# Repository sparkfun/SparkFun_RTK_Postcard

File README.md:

SparkFun RTK Postcard
========================================

[*SparkFun RTK Postcard (GPS-26916)*](https://www.sparkfun.com/sparkfun-rtk-postcard.html)

Designed and manufactured in Boulder, CO USA, the [SparkFun RTK Postcard](https://www.sparkfun.com/sparkfun-rtk-postcard.html) is a compact development board for your high-precision positioning and navigation needs. This board combines the Quectel LG290P GNSS RTK receiver with an Espressif ESP32-PICO-MINI-02 MCU module, running our latest [RTK Everywhere firmware](https://github.com/sparkfun/SparkFun_RTK_Everywhere_Firmware). The ESP32 provides the SparkFun Postcard with WiFi and Bluetooth&trade; connectivity to operate as an NTRIP caster or client. Meanwhile, the 4-pin locking JST-GH connector allows users to transmit or receive RTCMv3 messages for RTK corrections from a local base station.

- The LG290P module is a quad-band, multi-constellation, high-precision, RTK GNSS receiver. The module can simultaneously receive signals from the `L1`, `L2`, `L5`, and `L6`/`E6` frequency bands of the GPS, GLONASS, Galileo, BDS, QZSS, and NavIC GNSS constellations. In addition, the module supports SBAS augmentation systems (WASS, EGNOS, BDSBAS, MSAS, GAGAN, and SDCM), PPP services* (BDS PPP-B2b, QZSS CLAS, MADOCA-PPP, and Galileo HAS), RTCM, and RTK corrections for precision navigation with a fast convergence time and reliable performance. Connect with ease using a variety of interfaces, including UART, SPI*, and I2C*. 

- The ESP32-PICO-MINI-02 is a powerful MCU module with WiFi, Bluetooth&trade;, and BLE connectivity and comes integrated with 8MB SPI flash, 2MB SPI Pseudo static RAM (PSRAM), and a 40 MHz crystal oscillator. The ESP32 microcontroller itself features two CPU cores that can be individually controlled, with an adjustable clock frequency between 80 - 240MHz and a low-power co-processor for minor tasks, such as monitoring peripherals. It supports a range of peripherals including an SD card interface, capacitive touch sensors, ADC, DAC, Two-Wire Automotive Interface (TWAI), Ethernet, high-speed SPI, UART, I2S, I2C, etc.

With the [RTK Everywhere firmware](https://github.com/sparkfun/SparkFun_RTK_Everywhere_Firmware) that comes pre-loaded, users can seamlessly operate the RTK Postcard as a base station or rover. These modes also offer additional functions, based on the available, wireless communication options:

- The RTK Postcard can transmit or receive RTCMv3 messages locally by connecting one of our [SiK Telemetry radios](https://www.sparkfun.com/sik-telemetry-radio-v3-915mhz-100mw.html).
- Through WiFi or Bluetooth&trade;, the RTK Postcard can also function as an NTRIP caster or client.
- The RTK Postcard can transmit NMEA messages to a [graphical information software (GIS)](https://docs.sparkfun.com/SparkFun_RTK_Everywhere_Firmware/gis_software_android/) apps on any mobile device when paired as a Bluetooth&trade; device.

In addition to the RTK Postcard, we created the [Portability Shield](https://www.sparkfun.com/sparkfun-portability-shield.html) for the convenience of users. Simply connecting these products, provides a 1.3” OLED display and a five-way button to navigate the configuration settings and display PNT data; a microSD card slot for data logging; and a LiPo battery charger with a fuel gauge to take the RTK Postcard *"on-the-go"*. All of these will operate plug-and-play without the need for new code.

> [!NOTE]
> The [RTK Everywhere firmware](https://github.com/sparkfun/SparkFun_RTK_Everywhere_Firmware) is open-source, so users can obtain, check, and even modify the device's functionality. This allows for easier feature expansion, bug maintenance, and longer device longevity.

> [!NOTE]
> `*`: Feature is still under development

> [!IMPORTANT]
> - Currently, only the UART interface is supported by the LG290P module.
> - Additionally, the corrections for some of the PPP services may not be implemented yet.

Documentation
--------------

* **[Hookup Guide (mkdocs)](http://docs.sparkfun.com/SparkFun_RTK_Postcard/)** - The hookup guide for the SparkFun RTK Postcard hosted by GitHub pages.<br>
   
* [User Manual - RTK Everywhere Firmware](https://docs.sparkfun.com/SparkFun_RTK_Everywhere_Firmware/) - Documentation for the [RTK Everywhere firmware](https://github.com/sparkfun/SparkFun_RTK_Everywhere_Firmware)
* [SparkFun LG290P GNSS Arduino Library](https://github.com/sparkfun/SparkFun_LG290P_GNSS_Arduino_Library) - An Arduino library for the LG290P and LGx80P GNSS modules

*Need to download or print our hookup guide?*

* [Print *(Print to PDF)* from Single-Page View](http://docs.sparkfun.com/SparkFun_RTK_Postcard/print_view)

Repository Contents
-------------------

* **[/docs](/docs/)** - Online documentation files
    * [assets](/docs/assets/) - Assets files
        * [3d_model](/docs/assets/3d_model/) - Files for the 3D models
            * [3D CAD Model](/docs/assets/3d_model/cad_model.step) (.step)
        * [board_files](/docs/assets/board_files/) - Files for the product design
            * [KiCad Design Files](/docs/assets/board_files/kicad_files.zip) (.zip)
            * [Schematic](/docs/assets/board_files/schematic.pdf) (.pdf)
            * [Dimensions](/docs/assets/board_files/dimensions.pdf) (.pdf)
        * [component_documentation](/docs/assets/component_documentation/) - Datasheets for hardware components
        * [img/hookup_guide/](/docs/assets/img/hookup_guide/) - Images for hookup guide documentation
* **[/Enclosure](/Enclosure/)** - CAD model for an enclosure
* **[/Hardware](/Hardware/)** - Hardware design files (.brd, .sch)
  * **[/Production](/Production/)** - Production files

Product Variants
----------------

- LG290P Variants
  - [GPS-26916](https://www.sparkfun.com/sparkfun-rtk-postcard.html) - v1.0, Initial Release
  - [GPS-26620](https://www.sparkfun.com/sparkfun-quadband-gnss-rtk-breakout-lg290p-qwiic.html) - SparkFun Quadband GNSS RTK Breakout - LG290P (Qwiic) *(w/o ESP32)*
- [GPS-28019](https://www.sparkfun.com/products/28019) - SparkFun Quadband GNSS RTK Breakout - LG580P (Qwiic)

Version History
---------------

* [v10](https://github.com/sparkfun/SparkFun_RTK_Postcard/releases/tag/v10) - Initial Release

License Information
-------------------

This product is ***open source***!

Please review the [`LICENSE.md`](./LICENSE.md) file for license information.

If you have any questions or concerns about licensing, please contact technical support on our [SparkFun forums](https://community.sparkfun.com/).

Distributed as-is; no warranty is given.

- Your friends at SparkFun.

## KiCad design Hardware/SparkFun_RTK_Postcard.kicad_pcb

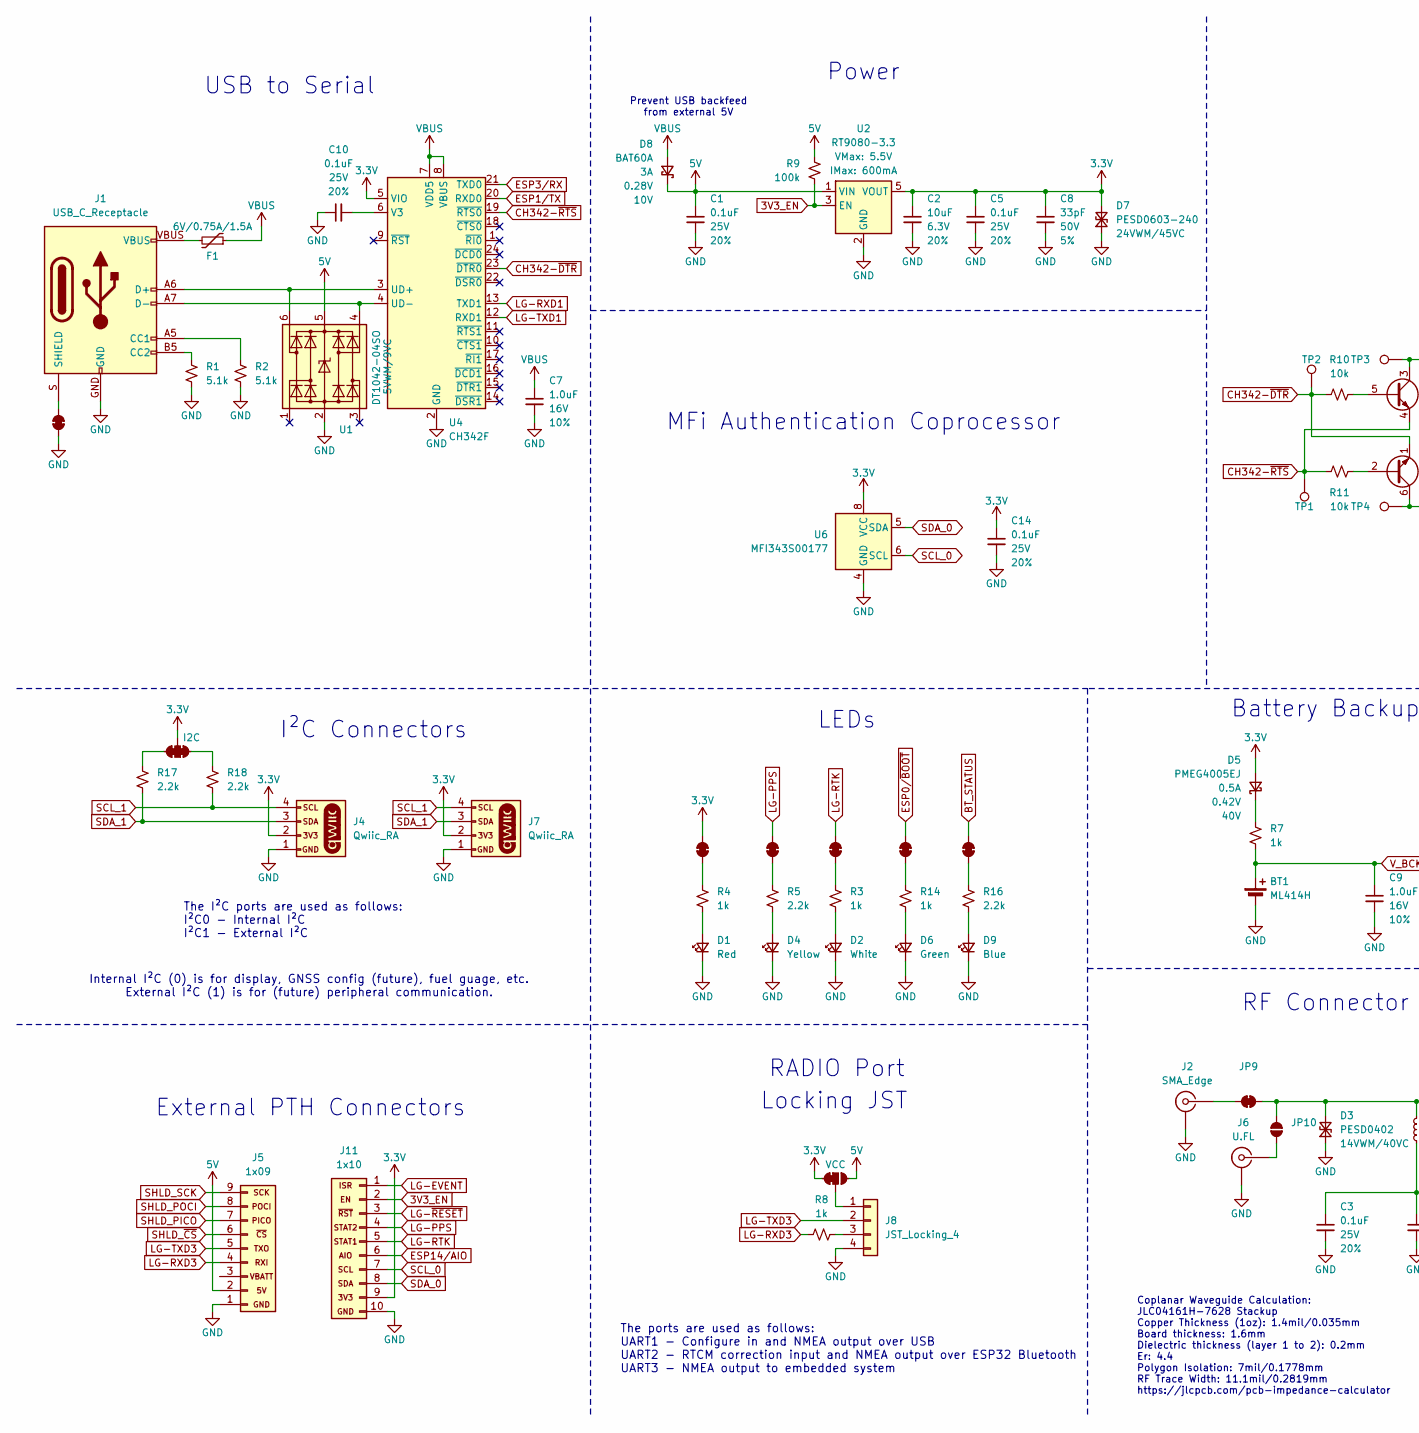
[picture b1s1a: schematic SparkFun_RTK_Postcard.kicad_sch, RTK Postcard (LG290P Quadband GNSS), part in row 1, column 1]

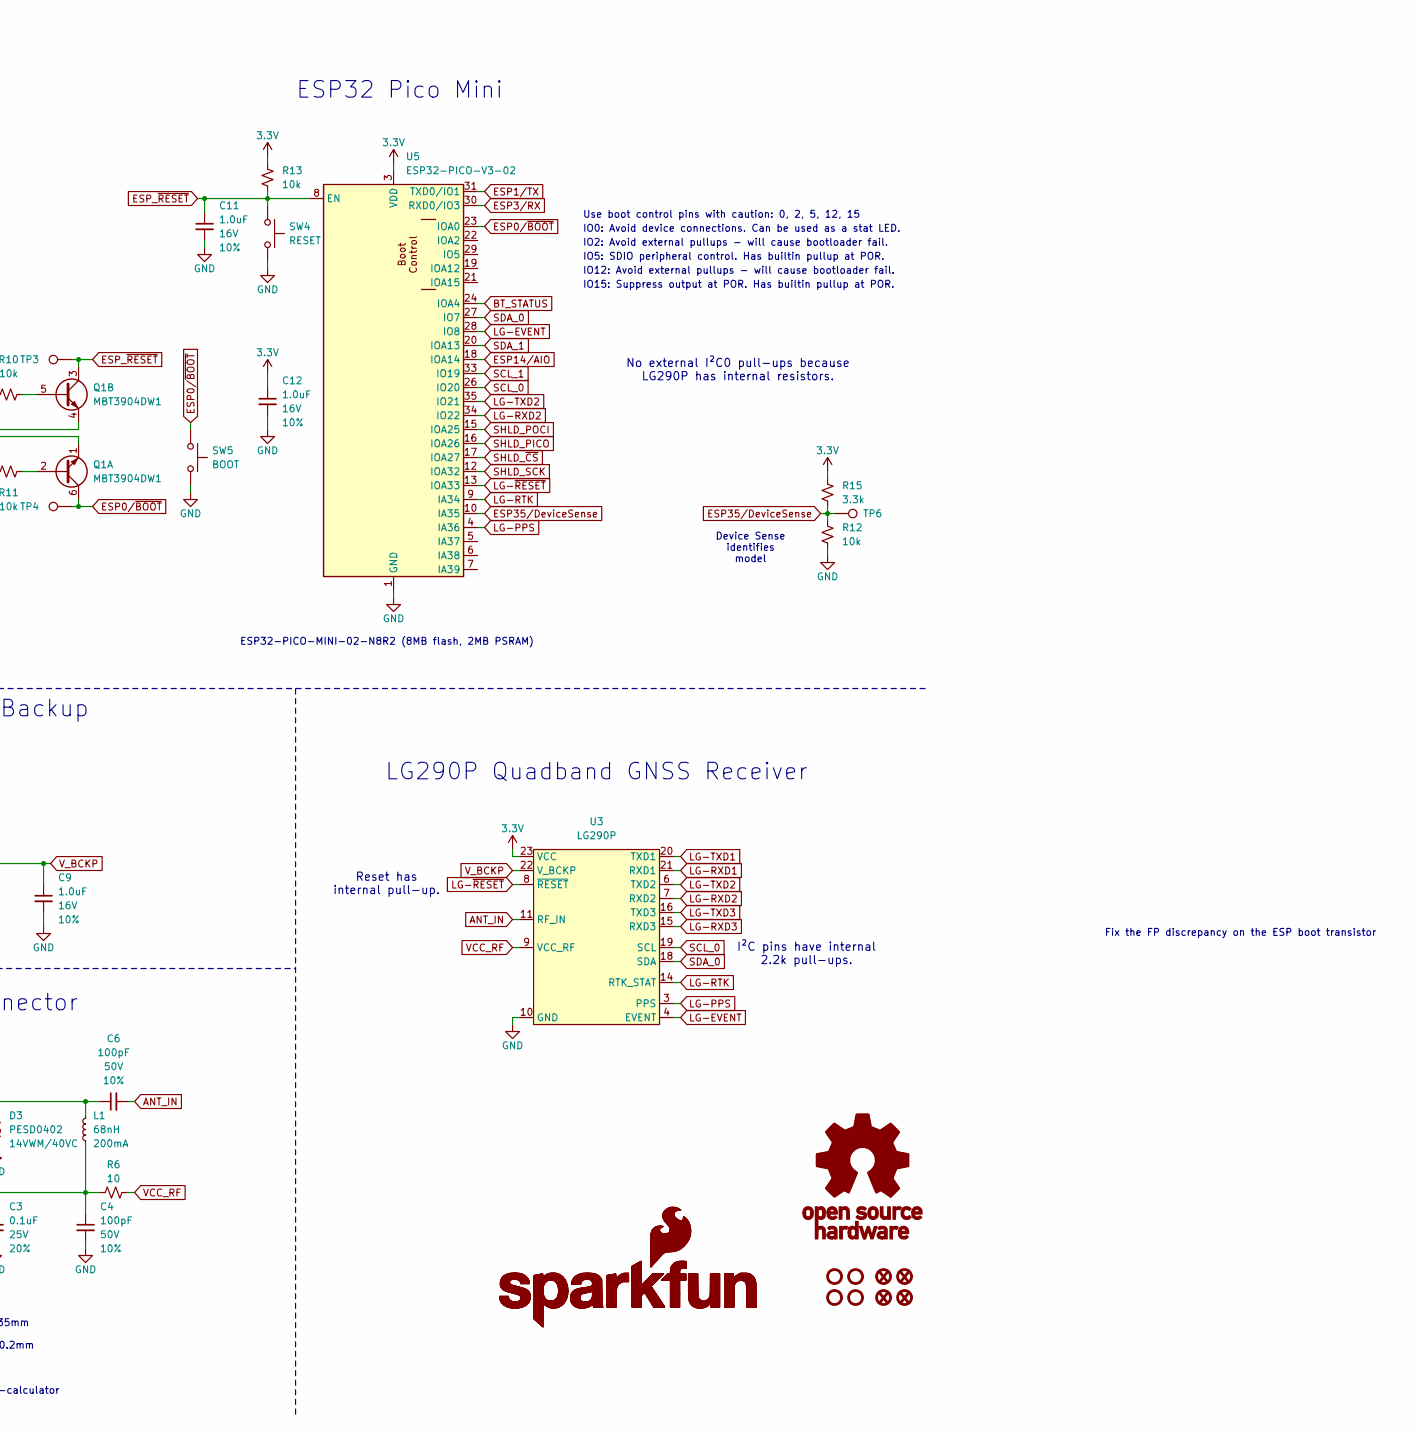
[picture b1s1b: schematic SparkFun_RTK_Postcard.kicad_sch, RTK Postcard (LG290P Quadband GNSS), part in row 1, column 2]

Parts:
BT1: ML414H; ML414H_IV01E
C1, C3, C5, C10, C14: 0.1uF; C_0603_1608Metric; Voltage 25V; Tolerance 20%
C2: 10uF; C_0603_1608Metric; Voltage 6.3V; Tolerance 20%
C4: 100pF; C_0603_1608Metric; Voltage 50V; Tolerance 10%
C6: 100pF; C_0402_1005Metric; Voltage 50V; Tolerance 10%
C7, C9, C11, C12: 1.0uF; C_0603_1608Metric; Voltage 16V; Tolerance 10%
C8: 33pF; C_0603_1608Metric; Voltage 50V; Tolerance 5%
D1: Red; LED_0603_1608Metric_Red
D2: White; LED_0603_1608Metric_White
D3: PESD0402; C_0402_1005Metric; Rating 14VWM/40VC
D4: Yellow; LED_0603_1608Metric_Yellow
D5: PMEG4005EJ; SOD-323
D6: Green; LED_0603_1608Metric_Green
D7: PESD0603-240; C_0603_1608Metric; Rating 24VWM/45VC
D8: BAT60A; SOD-323
D9: Blue; LED_0603_1608Metric_Blue
F1: 6V/0.75A/1.5A; 1206
FID1, FID2, FID3, FID4: Fiducial_0.5mm; Fiducial_0.5mm_Mask1mm
G1: OSHW_Logo; Creative_Commons_License
G3, G5: SparkFun_Logo
J1: USB_C_Receptacle; USB-C_16
J2: SMA_Edge; SMA_Edge_8mm
J4, J7: Qwiic_RA; JST_1x04_P1.0mm_Horizontal_SMD
J5: 1x09; 1x09_P2.54mm
J6: U.FL
J8: JST_Locking_4; JST_1x04_P1.25mm_Locking_Horizontal_SMD
J11: 1x10; 1x10_P2.54mm
JP1, JP2, JP3, JP5, JP7, JP8, JP9: Jumper_2_NC_Trace
JP4: VCC; Jumper_3_NC-1_Trace
JP6: I2C; Jumper_3_NC-2_Trace
JP10: Jumper_2_NO
L1: 68nH; C_0402_1005Metric
Q1: MBT3904DW1; SOT-363_SC-70-6
R1, R2: 5.1k; R_0603_1608Metric
R3, R4, R7, R8, R14: 1k; R_0603_1608Metric
R5, R16, R17, R18: 2.2k; R_0603_1608Metric
R6: 10; R_0603_1608Metric
R9: 100k; R_0603_1608Metric
R10, R11, R12, R13: 10k; R_0603_1608Metric
R15: 3.3k; R_0603_1608Metric
ST1, ST2, ST3, ST4: Standoff
SW4: RESET; Push_SMD_4.6x2.8mm_h2.5mm
SW5: BOOT; Push_SMD_4.6x2.8mm_h2.5mm
TP1, TP2, TP3, TP4, TP6: 1.0mm; TestPoint-1.0mm
U1: DT1042-04SO; SOT23-6; Rating 5VWM/9VC
U2: RT9080-3.3; SOT23-5
U3: LG290P; Quectel_LG290P
U4: CH342F; QFN-24-1EP_4x4mm_P0.5mm_EP2.7x2.7mm
U5: ESP32-PICO-V3-02; ESP32-PICO-MINI
U6: MFI343S00177; DFN-8_3x2mm_P0.5mm_EP1.66x1.5mm

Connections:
3.3V: C2.1, C5.1, C8.1, C12.1, C14.1, D5.2 (A), D7.2 (A2), J4.2, J7.2, J11.9, JP2.2 (B), JP4.1 (A), JP6.2 (B), R13.2, R15.2, U2.5 (VOUT), U3.23 (VCC), U4.5 (VIO), U5.3 (VDD), U6.8 (VCC)
3V3_EN: J11.2, R9.1, U2.3 (EN)
5V: C1.1, D8.1 (K), J5.2, JP4.3 (C), R9.2, U1.5 (VCC), U2.1 (VIN)
ANT_IN: C6.2, U3.11 (RF_IN)
BT_STATUS: JP1.2 (B), U5.24 (IOA4)
CH342-~DTR: Q1.1 (E1), R10.1, TP2.1, U4.23 (~DTR0)
CH342-~RTS: Q1.4 (E2), R11.1, TP1.1, U4.19 (~RTS0)
ESP0/~BOOT: JP8.2 (B), Q1.6 (C1), SW5.1, TP4.1, U5.23 (IOA0)
ESP1/TX: U4.20 (RXD0), U5.31 (TXD0/IO1)
ESP3/RX: U4.21 (TXD0), U5.30 (RXD0/IO3)
ESP14/AIO: J11.6, U5.18 (IOA14)
ESP35/DeviceSense: R12.2, R15.1, TP6.1, U5.10 (IA35)
ESP_~RESET: C11.1, Q1.3 (C2), R13.1, SW4.1, TP3.1, U5.8 (EN)
GND: BT1.-, C1.2, C2.2, C3.2, C4.2, C5.2, C7.2, C8.2, C9.2, C10.1, C11.2, C12.2, C14.2, D1.1 (K), D2.1 (K), D3.1 (A1), D4.1 (K), D6.1 (K), D7.1 (A1), D9.1 (K), J1.GND, J2.2 (Ext), J4.1, J5.1, J6.2 (Ext), J7.1, J8.4, J11.10, JP7.1 (A), R1.1, R2.1, R12.1, SW4.2, SW5.2, U1.2 (GND), U2.2 (GND), U3.10 (GND), U3.12 (GND), U3.13 (GND), U3.24 (GND), U3.25 (GND), U4.2 (GND), U4.25 (GND), U5.1 (GND), U5.2 (GND), U5.11 (GND), U5.14 (GND), U5.36 (GND), U5.37 (GND), U5.38 (GND), U5.39 (GND), U5.40 (GND), U5.41 (GND), U5.42 (GND), U5.43 (GND), U5.44 (GND), U5.45 (GND), U5.46 (GND), U5.47 (GND), U5.48 (GND), U5.49.1 (GND), U5.49.2 (GND), U5.49.3 (GND), U5.49.4 (GND), U5.49.5 (GND), U5.49.6 (GND), U5.49.7 (GND), U5.49.8 (GND), U5.49.9 (GND), U5.50 (GND), U5.51 (GND), U5.52 (GND), U5.53 (GND), U6.1 (GND), U6.4 (GND), U6.7 (GND)
LG-EVENT: J11.1, U3.4 (EVENT), U5.28 (IO8)
LG-PPS: J11.4, JP3.2 (B), U3.3 (PPS), U5.4 (IA36)
LG-RTK: J11.5, JP5.2 (B), U3.14 (RTK_STAT), U5.9 (IA34)
LG-RXD1: U3.21 (RXD1), U4.13 (TXD1)
LG-RXD2: U3.7 (RXD2), U5.34 (IO22)
LG-RXD3: J5.4, R8.2, U3.15 (RXD3)
LG-TXD1: U3.20 (TXD1), U4.12 (RXD1)
LG-TXD2: U3.6 (TXD2), U5.35 (IO21)
LG-TXD3: J5.5, J8.2, U3.16 (TXD3)
LG-~RESET: J11.3, U3.8 (~RESET), U5.13 (IOA33)
unnamed: C3.1, C4.1, L1.1, R6.1
unnamed: D1.2 (A), R4.1
unnamed: D2.2 (A), R3.1
unnamed: C6.1, D3.2 (A2), JP9.2 (B), JP10.2 (B), L1.2
unnamed: D4.2 (A), R5.1
unnamed: D5.1 (K), R7.2
unnamed: D6.2 (A), R14.1
unnamed: D9.2 (A), R16.1
unnamed: F1.2, J1.VBUS
unnamed: J1.A5 (CC1), R2.2
unnamed: J1.B5 (CC2), R1.2
unnamed: J1.S (SHIELD), JP7.2 (B)
unnamed: J2.1 (In), JP9.1 (A)
unnamed: J6.1 (In), JP10.1 (A)
unnamed: J8.1, JP4.2 (B)
unnamed: J8.3, R8.1
unnamed: JP1.1 (A), R16.2
unnamed: JP2.1 (A), R4.2
unnamed: JP3.1 (A), R5.2
unnamed: JP5.1 (A), R3.2
unnamed: JP6.1 (A), R18.2
unnamed: JP6.3 (C), R17.2
unnamed: JP8.1 (A), R14.2
unnamed: Q1.2 (B1), R11.2
unnamed: Q1.5 (B2), R10.2
unnamed: J1.A7 (D-), J1.B7 (D-), U1.4 (I/O3), U4.4 (UD-)
unnamed: J1.A6 (D+), J1.B6 (D+), U1.6 (I/O4), U4.3 (UD+)
unnamed: C10.2, U4.6 (V3)
SCL_0: J11.7, U3.19 (SCL), U5.26 (IO20), U6.6 (SCL)
SCL_1: J4.4, J7.4, R18.1, U5.33 (IO19)
SDA_0: J11.8, U3.18 (SDA), U5.27 (IO7), U6.5 (SDA)
SDA_1: J4.3, J7.3, R17.1, U5.20 (IOA13)
SHLD_PICO: J5.7, U5.16 (IOA26)
SHLD_POCI: J5.8, U5.15 (IOA25)
SHLD_SCK: J5.9, U5.12 (IOA32)
SHLD_~CS: J5.6, U5.17 (IOA27)
VBUS: C7.1, D8.2 (A), F1.1, U4.7 (VDD5), U4.8 (VBUS)
VCC_RF: R6.2, U3.9 (VCC_RF)
V_BCKP: BT1.+, C9.1, R7.1, U3.22 (V_BCKP)

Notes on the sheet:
The I²C ports are used as follows: I²C0 - Internal I²C I²C1 - External I²C
MFi Authentication Coprocessor
ESP32-PICO-MINI-02-N8R2 (8MB flash, 2MB PSRAM)
I²C Connectors
IO15: Suppress output at POR. Has builtin pullup at POR.
Prevent USB backfeed from external 5V
The ports are used as follows: UART1 - Configure in and NMEA output over USB UART2 - RTCM correction input and NMEA output over ESP32 Bluetooth UART3 - NMEA output to embedded system
Use boot control pins with caution: 0, 2, 5, 12, 15
ESP32 Pico Mini
IO2: Avoid external pullups - will cause bootloader fail.
Internal I²C (0) is for display, GNSS config (future), fuel guage, etc. External I²C (1) is for (future) peripheral communication.
Reset has internal pull-up.
IO0: Avoid device connections. Can be used as a stat LED.
Coplanar Waveguide Calculation: JLC04161H-7628 Stackup Copper Thickness (1oz): 1.4mil/0.035mm Board thickness: 1.6mm Dielectric thickness (layer 1 to 2): 0.2mm Er: 4.4 Polygon Isolation: 7mil/0.1778mm RF Trace Width: 11.1mil/0.2819mm https://jlcpcb.com/pcb-impedance-calculator
I²C pins have internal 2.2k pull-ups.
Locking JST
Power
RF Connector
LEDs
LG290P Quadband GNSS Receiver
Fix the FP discrepancy on the ESP boot transistor
IO12: Avoid external pullups - will cause bootloader fail.
IO5: SDIO peripheral control. Has builtin pullup at POR.
RADIO Port
USB to Serial
Battery Backup
Device Sense identifies model
External PTH Connectors
No external I²C0 pull-ups because LG290P has internal resistors.

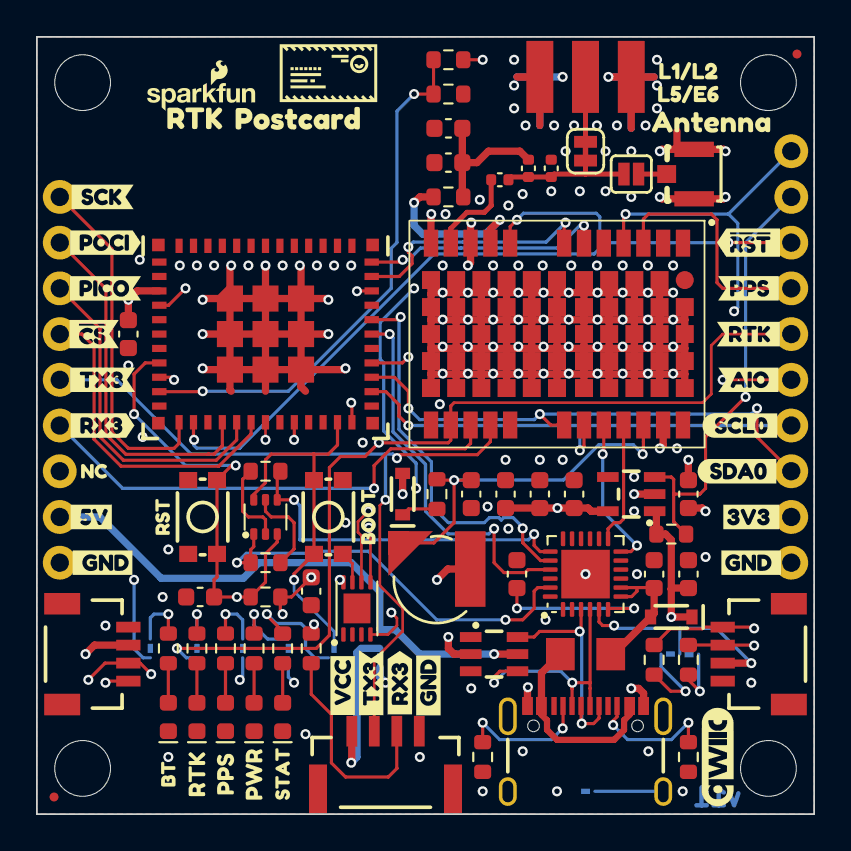
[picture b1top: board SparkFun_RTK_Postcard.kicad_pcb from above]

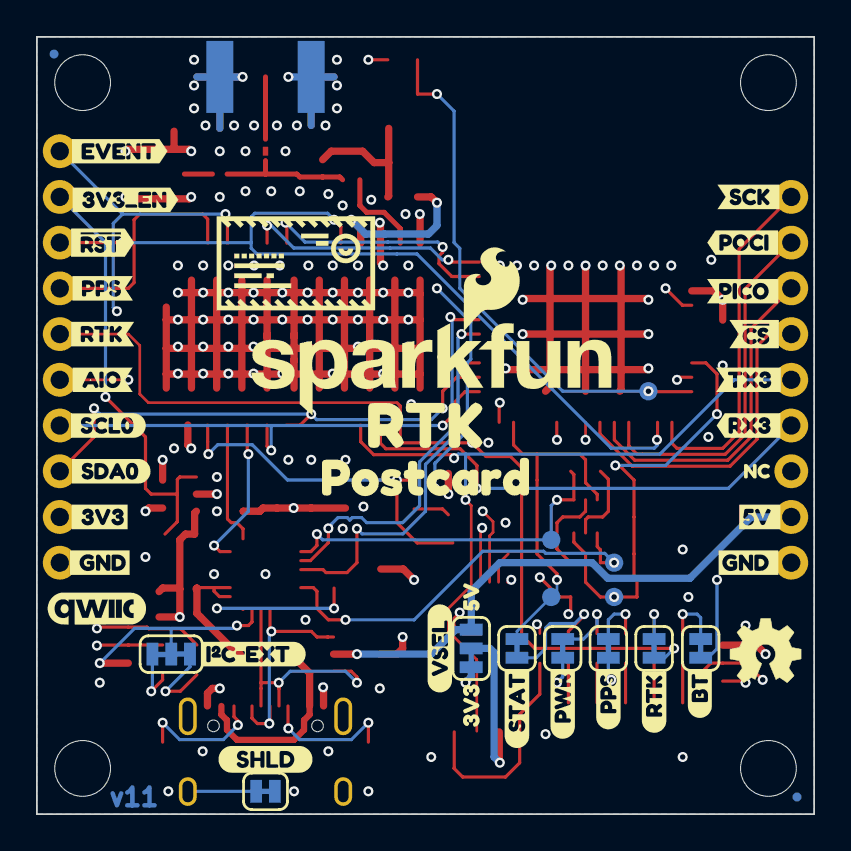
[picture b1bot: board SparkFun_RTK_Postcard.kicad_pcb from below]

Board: 4 copper layers, 43.2 x 43.2 mm, 149 parts (47 on the bottom side), 63 nets.

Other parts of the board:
Ref**: Val**; OSHW_Logo_4mm
kibuzzard-64C2E6A3: G***; kibuzzard-64C2E6A3
kibuzzard-64C2E6BD: G***; kibuzzard-64C2E6BD
kibuzzard-64C2E6D6: G***; kibuzzard-64C2E6D6
kibuzzard-64C2EB16: G***; kibuzzard-64C2EB16
kibuzzard-64C3DF93: G***; kibuzzard-64C3DF93
kibuzzard-66CB82FB: G***; kibuzzard-66CB82FB
kibuzzard-66CB829C: G***; kibuzzard-66CB829C
kibuzzard-66CB830B: G***; kibuzzard-66CB830B
kibuzzard-66E505A3: G***; kibuzzard-66E505A3
kibuzzard-66E5016F: G***; kibuzzard-66E5016F
kibuzzard-66E5059C: G***; kibuzzard-66E5059C
kibuzzard-66E50481: G***; kibuzzard-66E50481
kibuzzard-66E50489: G***; kibuzzard-66E50489
kibuzzard-66F2CCE8: G***; kibuzzard-66F2CCE8
kibuzzard-66F2CD12: G***; kibuzzard-66F2CD12
kibuzzard-66F2CD24: G***; kibuzzard-66F2CD24
kibuzzard-66F2CD30: G***; kibuzzard-66F2CD30
kibuzzard-66F31A0F: G***; kibuzzard-66F31A0F
kibuzzard-66F31A40: G***; kibuzzard-66F31A40
kibuzzard-66F31A48: G***; kibuzzard-66F31A48
kibuzzard-66F31A50: G***; kibuzzard-66F31A50
kibuzzard-66F31A58: G***; kibuzzard-66F31A58
kibuzzard-66F31A60: G***; kibuzzard-66F31A60
kibuzzard-66F31A71: G***; kibuzzard-66F31A71
kibuzzard-66F31A78: G***; kibuzzard-66F31A78
kibuzzard-66F31AC6: G***; kibuzzard-66F31AC6
kibuzzard-66F31AD0: G***; kibuzzard-66F31AD0
kibuzzard-66F31AE7: G***; kibuzzard-66F31AE7
kibuzzard-66F31B2D: G***; kibuzzard-66F31B2D
kibuzzard-66F31B4A: G***; kibuzzard-66F31B4A
kibuzzard-66F31B4F: G***; kibuzzard-66F31B4F
kibuzzard-66F31B16: G***; kibuzzard-66F31B16
kibuzzard-66F31B25: G***; kibuzzard-66F31B25
kibuzzard-66F31B33: G***; kibuzzard-66F31B33
kibuzzard-66F31D00: G***; kibuzzard-66F31D00
kibuzzard-66F318A4: G***; kibuzzard-66F318A4
kibuzzard-66F318AF: G***; kibuzzard-66F318AF
kibuzzard-66F318EE: G***; kibuzzard-66F318EE
kibuzzard-66F3185F: G***; kibuzzard-66F3185F
kibuzzard-66F3186F: G***; kibuzzard-66F3186F
kibuzzard-66F3187E: G***; kibuzzard-66F3187E
kibuzzard-66F3190E: G***; kibuzzard-66F3190E
kibuzzard-66F3194C, kibuzzard-66F3194C#2: G***; kibuzzard-66F3194C
kibuzzard-66F3756F: G***; kibuzzard-66F3756F
kibuzzard-66F31920: G***; kibuzzard-66F31920
kibuzzard-66F31933: G***; kibuzzard-66F31933
kibuzzard-66F31954, kibuzzard-66F31954#2: G***; kibuzzard-66F31954
kibuzzard-66F31960: G***; kibuzzard-66F31960
kibuzzard-66F31965, kibuzzard-66F31965#2: G***; kibuzzard-66F31965
kibuzzard-66F37583: G***; kibuzzard-66F37583
kibuzzard-672EE142: G***; kibuzzard-672EE142
kibuzzard-672EE156: G***; kibuzzard-672EE156
kibuzzard-672FC5C6: G***; kibuzzard-672FC5C6
kibuzzard-672FC5CC: G***; kibuzzard-672FC5CC
kibuzzard-672FC6B5: G***; kibuzzard-672FC6B5
kibuzzard-672FC715: G***; kibuzzard-672FC715
kibuzzard-672FC890: G***; kibuzzard-672FC890
kibuzzard-672FC894: G***; kibuzzard-672FC894
kibuzzard-673B9839, kibuzzard-673B9839#2: G***; kibuzzard-673B9839
kibuzzard-6724512A: G***; kibuzzard-6724512A

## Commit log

2024-09-25 Rotate silkscreen. Add AIO pin.
2024-11-09 Fix PPS. Add SMA. Change to 1.6mm. Add BT LED. Add I2C bus. Connect RST to LG290P..
2024-11-12 Add panel
2024-11-19 Add panel files
2024-11-27 Update README.md
    Vaporware Release
2024-12-18 Add housing 3D file
2024-12-19 Update README.md
    New product picture
2024-12-21 Initial Setup and Docs Draft
2025-01-02 Reduce paste on ESP32. Update to smaller schematic symbols.
    Change to SparkFun library LG290P version.
2025-01-02 Update panel files
2025-01-07 Update sch/pcb with smaller sch parts. Update prod panel with 10% paste reduction.
2025-01-07 Update design files
2025-01-07 Deployed 137e95c with MkDocs version: 1.6.1
2025-01-07 Deployed b7a8342 with MkDocs version: 1.6.1
2025-01-07 Deployed b9c4661 with MkDocs version: 1.6.1
2025-01-07 Deployed 1e52fcc with MkDocs version: 1.6.1
2025-01-07 Deployed 0bd4de6 with MkDocs version: 1.6.1
2025-01-07 Deployed 403272d with MkDocs version: 1.6.1
2025-01-07 Deployed 8aa5b22 with MkDocs version: 1.6.1
2025-01-07 Deployed 405d0f4 with MkDocs version: 1.6.1
2025-01-07 Deployed 17ef69e with MkDocs version: 1.6.1
2025-01-07 Deployed db36ef3 with MkDocs version: 1.6.1
2025-01-08 Create generate_documentation.yml
    Workflow to build and deploy the documentation using mkdocs-material theme
2025-01-08 Fix link for badge
2025-01-08 Deployed 500d5bc with MkDocs version: 1.6.1
2025-01-13 Add firmware v3 and v4.
2025-01-13 Deployed ada6c0e with MkDocs version: 1.6.1
2025-01-14 Add docs to match v04 firmware.
2025-01-14 Deployed 28a854e with MkDocs version: 1.6.1
2025-01-23 Correct resistor package : 402 -> 0402
2025-01-23 Deployed 0fc4de4 with MkDocs version: 1.6.1
2025-02-14 Add v04 beta firmware to fix GST issue
2025-02-14 Deployed 57ac3ff with MkDocs version: 1.6.1
2025-02-20 Update introduction.md
    Updating missing image
2025-02-20 Deployed f3ccf5d with MkDocs version: 1.6.1
2025-02-20 Update introduction.md
    Adding image for RTK Everywhere Firmware
2025-02-20 Deployed d32b136 with MkDocs version: 1.6.1
2025-02-21 Update introduction.md
    Replace image crop
    Link to thumbnail for the RTK Everywhere Product Manual
    Fix search parameters
2025-02-21 Deployed 425f50e with MkDocs version: 1.6.1
2025-02-25 Add Beta 0224
    Should fix orthometric height issue
2025-02-25 Deployed 97d2c48 with MkDocs version: 1.6.1
2025-05-19 Add Quectel firmware v05
2025-05-19 Deployed f2b076b with MkDocs version: 1.6.1
2025-07-01 Update link to v2.1 QGNSS
2025-07-01 Deployed 7f0861a with MkDocs version: 1.6.1
2025-07-01 Deployed 2d20bc6 with MkDocs version: 1.6.1
2025-07-01 Deployed 871fc44 with MkDocs version: 1.6.1
2025-07-09 Remove authors plugin
    Removes mkdocs-git-authors-plugin
2025-07-09 Update QGNSS versioning
    Revised from v2.0 to v2.x
    Link redirects to latest software
2025-07-09 Add LG290P firmware update
    Added a new section to the documentation detailing the firmware update process for the LG290P module, including references to the official upgrade manual, links to firmware resources, and specific in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
2025-07-09 Update purchase link
    Revised the QR code and purchase button layout
2025-07-09 Replace center tag
    Updated documentation for deprecated <center> tags
    - Replaced w/ `<article style="text-align: center;" markdown>`
    - For video blocks `<article class="video-500px" style="text-align: center; margin: auto;" markdown>`
2025-07-09 Deployed 50125f3 with MkDocs version: 1.6.1
2025-07-09 Fix indentation
    Removed unnecessary tab indentation for the QGNSS software download button
2025-07-09 Deployed 8890b3a with MkDocs version: 1.6.1
2025-09-10 Update .gitignore
    Remove leftover merge conflict markers
    Consolidate duplicate entries
2025-09-10 Add v03 Beta firmware that includes HAS/E6 support
    Note: this version does not have v04 or v05 improvements already in production releases.
2025-09-10 Add protocol spec for v05 firmware
2025-09-10 Deployed e3fb031 with MkDocs version: 1.6.1
2025-09-12 Delete LG209P.bak
    Remove ignored file type
2025-09-12 Deployed 69d8e98 with MkDocs version: 1.6.1
2025-09-12 Add v06 Test firmware
    New beta version for the PPP function, which includes several optimizations. It is now based on the latest 'v05' firmware. "Entering the PPP floating stage means that convergence has occurred."
2025-09-12 Deployed ad25acb with MkDocs version: 1.6.1
2025-09-15 Remove directory
    Files were moved to the /docs/assets/component_documentation directory
2025-09-15 Update KiCAD files
    Updated file path, orientation, and location of footprints
2025-09-15 Update component documentation
    Updates the datasheet, manuals, application notes, etc. for the LG290P
2025-09-15 Deployed fdf346a with MkDocs version: 1.6.1
2025-09-15 Deployed 7f7346c with MkDocs version: 1.6.1
2025-09-23 Deployed cbeaf6e with MkDocs version: 1.6.1
2025-09-23 Update product URLs
    Updated for SEO compatibility
2025-09-23 Deployed 65887db with MkDocs version: 1.6.1
2025-11-20 Add v06 PPP beta firmware
2025-11-20 Add full release v1.1 protocol
2025-11-20 Deployed 7b00ed5 with MkDocs version: 1.6.1
2025-12-16 Add LG290P firmware v06 with RTKHOLD feature
2025-12-16 Deployed bc7021b with MkDocs version: 1.6.1
2026-01-29 Push v2.01 (official HAS support) LG290P firmware
2026-01-29 Deployed d62b759 with MkDocs version: 1.6.1
2026-02-04 Move old firmware into subfolder. Add updated interface protocol.
2026-02-04 Deployed fb1501a with MkDocs version: 1.6.1
2026-02-07 Update to v9 and current libraries.
2026-02-07 Deployed 549f6c1 with MkDocs version: 1.6.1
2026-02-16 Added .step files for printing a thicker enclosure
    Notes: Thicker Housing Enclosures for the SparkFun RTK Postcard and Portability Shield combination
    There are two .step files (depending on how you connect the two modules):
    -------------------------
    Housing 2 v10 cc1-3.3mm.step (extra 3.3mm thick)
    - if soldering the two boards together with a set of male headers with just enough gap for a battery
    - the minimal thickness is a nice feature
2026-02-17 Add MFi. Update symbols. Use main library sym/fps.
2026-02-17 Add interface protocol for older firmware version.
2026-02-17 Deployed 981abef with MkDocs version: 1.6.1
2026-02-17 Deployed d85ed71 with MkDocs version: 1.6.1
2026-03-04 Add v2.1 'debug' version
2026-03-04 Deployed 2de2959 with MkDocs version: 1.6.1
2026-06-03 Deployed 2f3d3e7 with MkDocs version: 1.6.1
2026-06-03 Update formatting
2026-06-03 Update forum link
2026-06-03 Update copyright
2026-06-03 Fix MathJax and KaTeX
2026-06-03 Update troubleshooting_tips.md
    Add information about antenna capabilities
2026-06-03 Update workflow
2026-06-03 Link LG580P
2026-06-03 Deployed b3ba1d4 with MkDocs version: 1.6.1

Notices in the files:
parts and their libraries:
Released under the Creative Commons Attribution Share-Alike 4.0 License
https://creativecommons.org/licenses/by-sa/4.0
